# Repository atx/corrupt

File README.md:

# corrupt
A 65% keyboard with a somewhat non-standard layout. Inspired by the KBT Pure Pro.

### Specs

 * Standard GH60-style case support
 * MX-style switches
 * 2U left shift (bottom row shifted by 0.25U to the left)
 * Standard 6.25U spacebar
 * USB-C (wired-only)
 * [zmk port](https://github.com/atx/zmk/tree/corrupt)
 * Compatible FR4 plate included in the repository
 * Under-the-spacebar WE-SKEDD debugging port
 * STM32F405 MCU (total overkill)
 * Both the key plate and the PCB can be manufactured by JLC, most components are available for PCBA

### Layout

### Debugging connector

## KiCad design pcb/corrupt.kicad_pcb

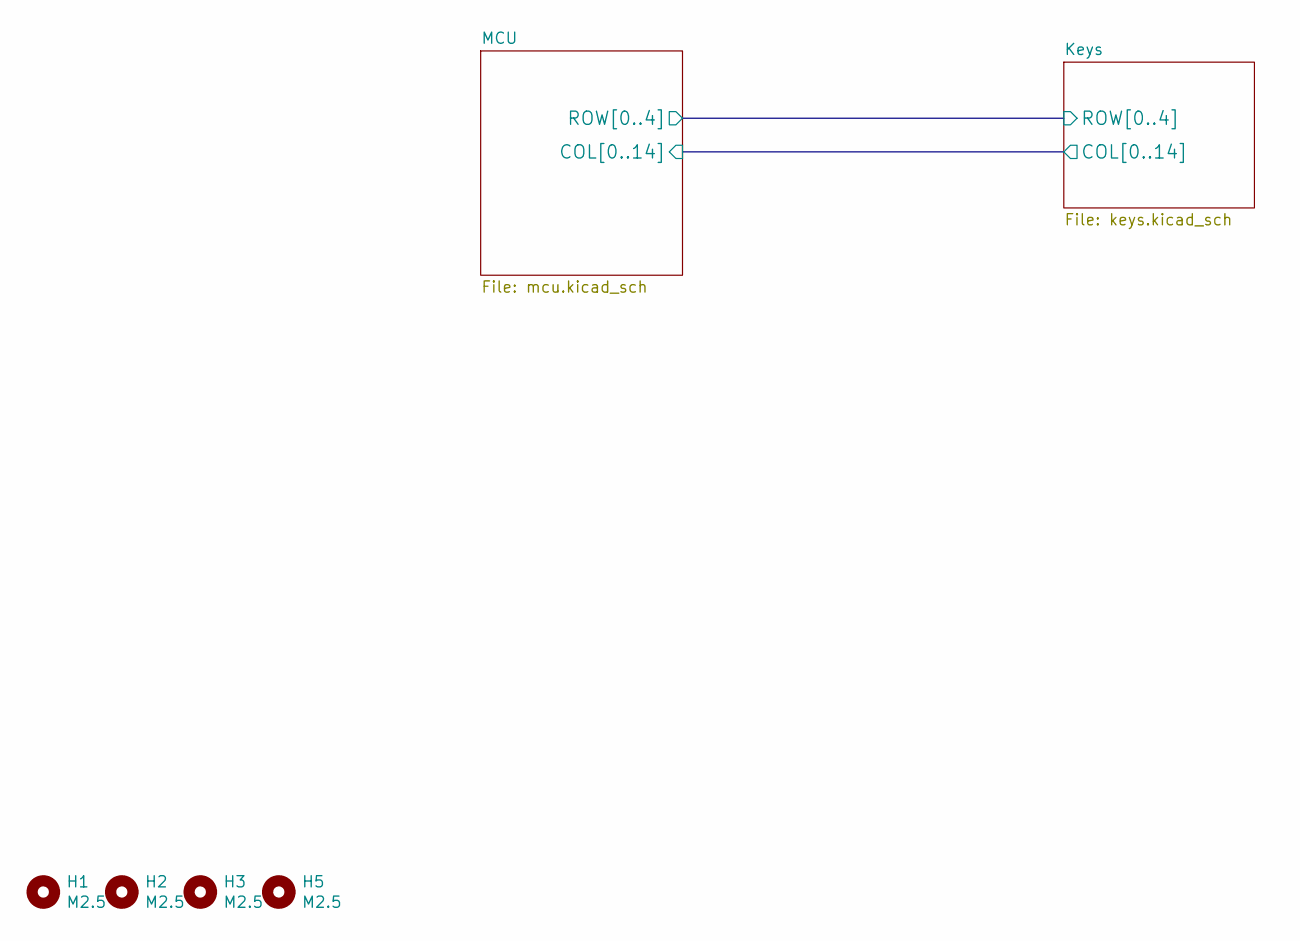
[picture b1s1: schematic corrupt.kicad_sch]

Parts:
H1, H2, H3, H5: M2.5; MountingHole_2.7mm_M2.5_Pad

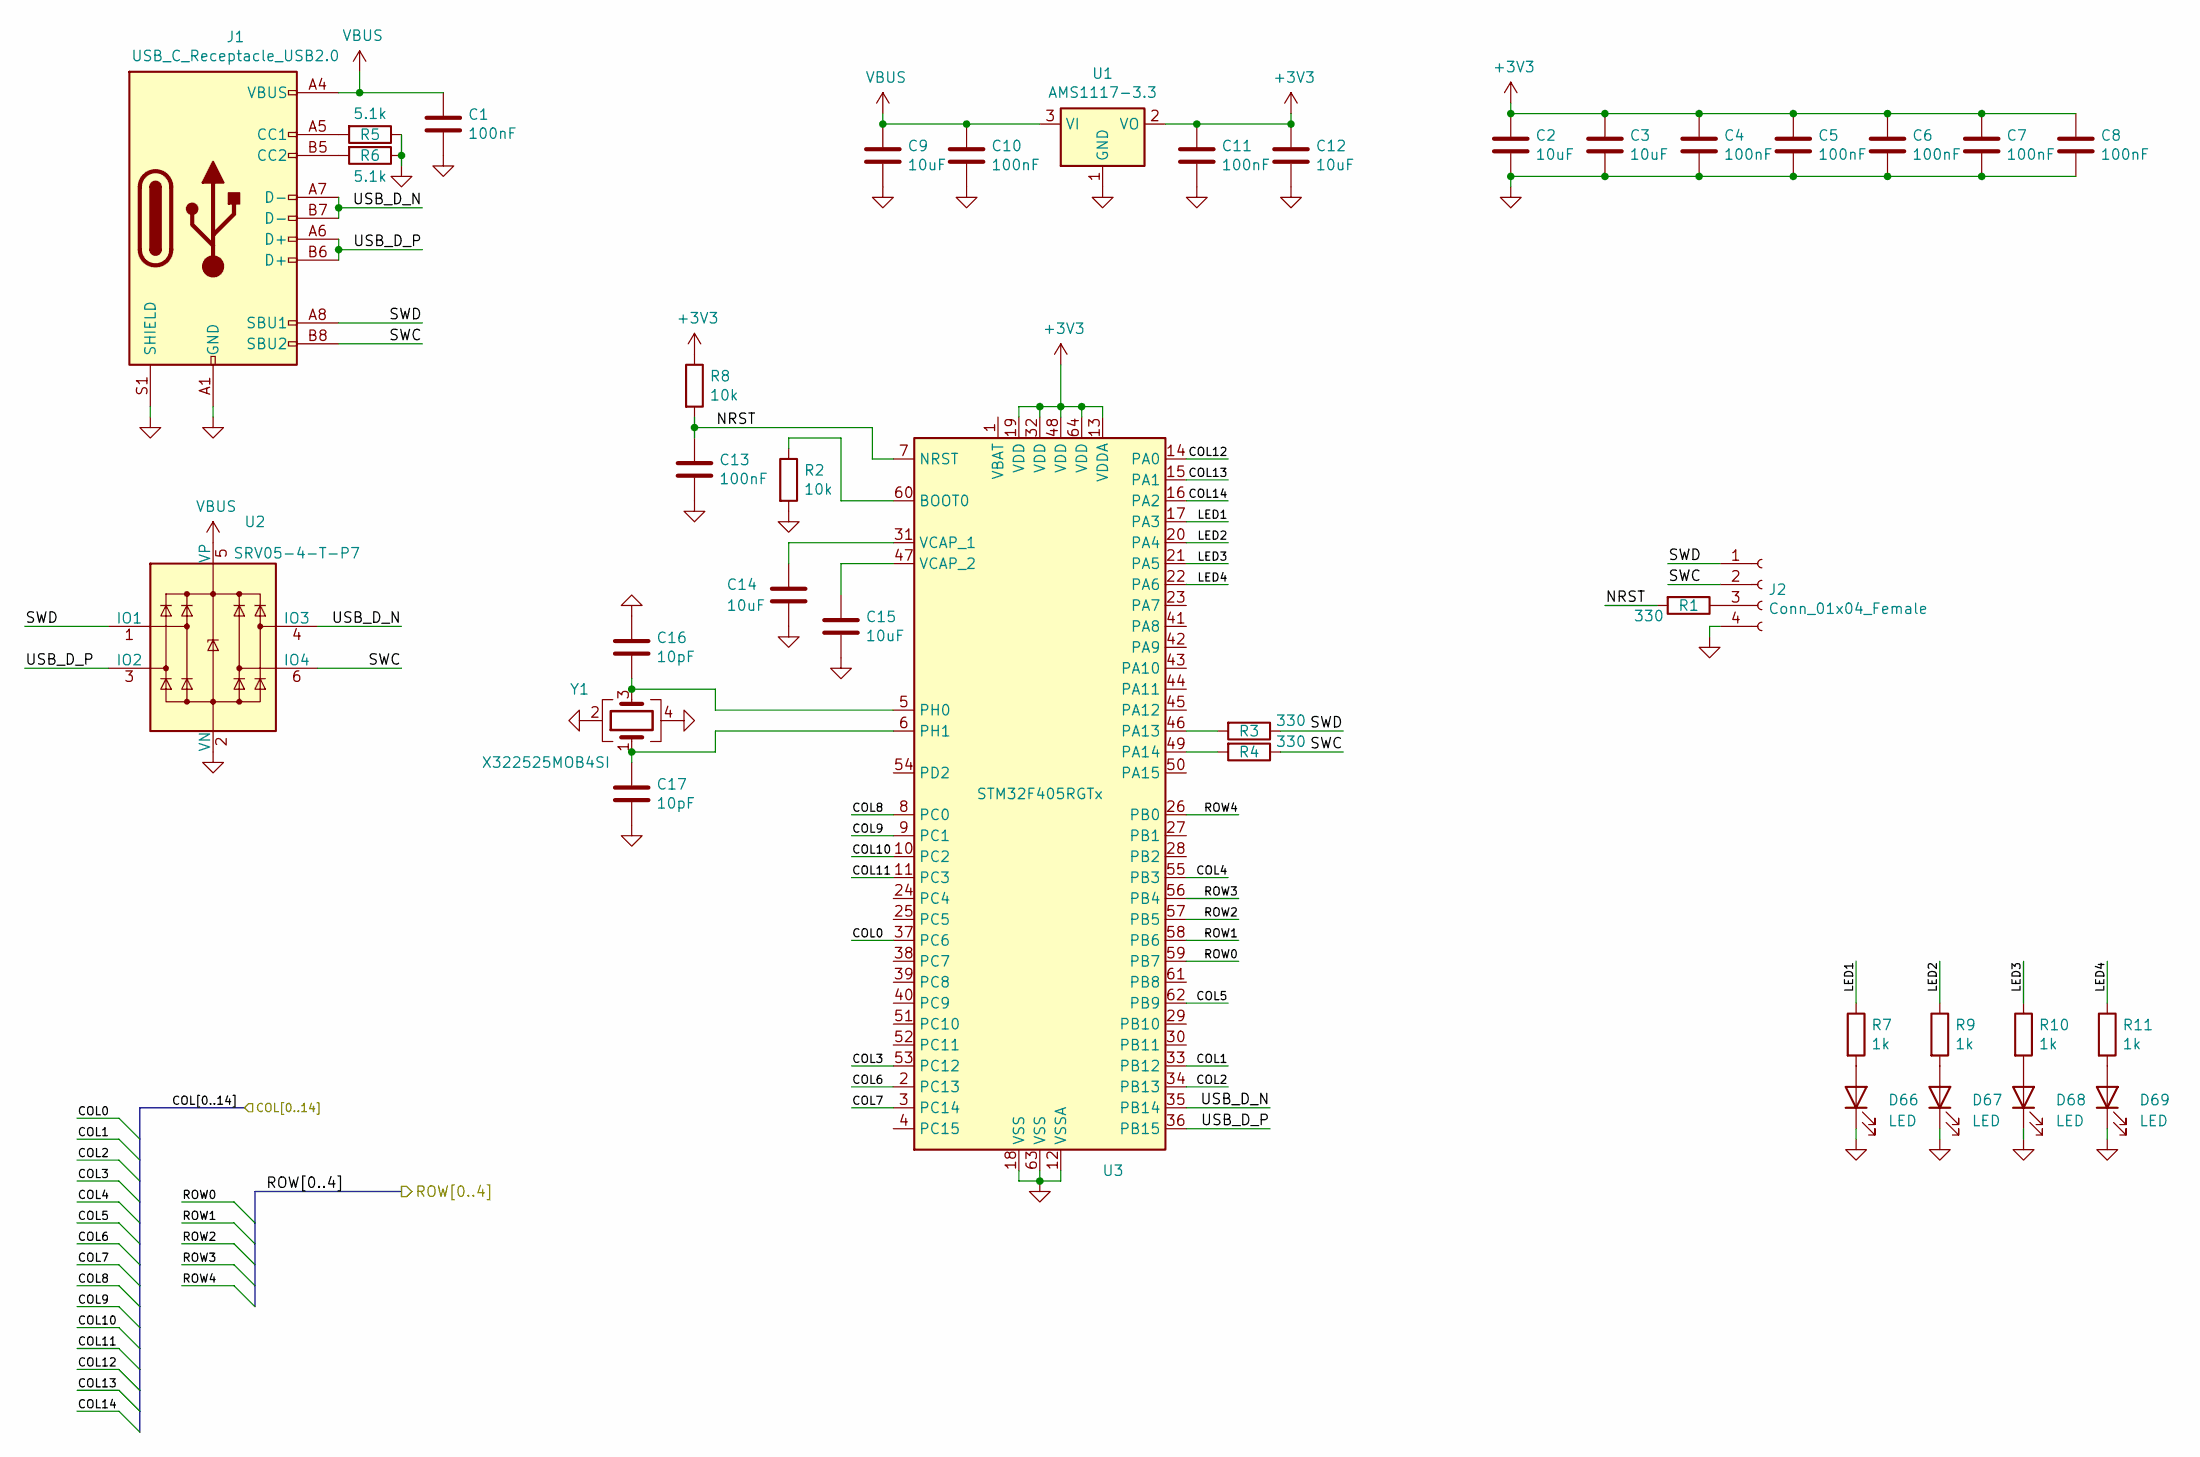
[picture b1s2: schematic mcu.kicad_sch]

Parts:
C1, C4, C5, C6, C7, C8, C10, C11, C13: 100nF; C_0402_1005Metric; LCSC C1525
C2, C3, C9, C12, C14, C15: 10uF; C_0603_1608Metric; LCSC C19702
C16, C17: 10pF; C_0402_1005Metric; LCSC C32949
D66, D67, D68, D69: LED; LED_0603_1608Metric
J1: USB_C_Receptacle_USB2.0; USB_C_Receptacle_Palconn_UTC16-G
J2: Conn_01x04_Female; WR-WST-4P-DBG
R1, R3, R4: 330; R_0402_1005Metric; LCSC C25104
R2, R8: 10k; R_0402_1005Metric; LCSC C25744
R5, R6: 5.1k; R_0402_1005Metric; LCSC C25905
R7, R9, R10, R11: 1k; R_0402_1005Metric; LCSC C11702
U1: AMS1117-3.3; SOT-223-3_TabPin2; LCSC C6186
U2: SRV05-4-T-P7; SOT-23-6; LCSC C7420376
U3: STM32F405RGTx; LQFP-64_10x10mm_P0.5mm; LCSC C15742
Y1: X322525MOB4SI; Crystal_SMD_3225-4Pin_3.2x2.5mm; LCSC C9006

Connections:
+3V3: C2.1, C3.1, C4.1, C5.1, C6.1, C7.1, C8.1, C11.1, C12.1, R8.1, U1.2 (VO), U3.13 (VDDA), U3.19 (VDD), U3.32 (VDD), U3.48 (VDD), U3.64 (VDD)
/Keys/COL0: U3.37 (PC6); also elsewhere on the board
/Keys/COL1: U3.33 (PB12); also elsewhere on the board
/Keys/COL2: U3.34 (PB13); also elsewhere on the board
/Keys/COL3: U3.53 (PC12); also elsewhere on the board
/Keys/COL4: U3.55 (PB3); also elsewhere on the board
/Keys/COL5: U3.62 (PB9); also elsewhere on the board
/Keys/COL6: U3.2 (PC13); also elsewhere on the board
/Keys/COL7: U3.3 (PC14); also elsewhere on the board
/Keys/COL8: U3.8 (PC0); also elsewhere on the board
/Keys/COL9: U3.9 (PC1); also elsewhere on the board
/Keys/COL10: U3.10 (PC2); also elsewhere on the board
/Keys/COL11: U3.11 (PC3); also elsewhere on the board
/Keys/COL12: U3.14 (PA0); also elsewhere on the board
/Keys/COL13: U3.15 (PA1); also elsewhere on the board
/Keys/COL14: U3.16 (PA2); also elsewhere on the board
/Keys/ROW0: U3.59 (PB7); also elsewhere on the board
/Keys/ROW1: U3.58 (PB6); also elsewhere on the board
/Keys/ROW2: U3.57 (PB5); also elsewhere on the board
/Keys/ROW3: U3.56 (PB4); also elsewhere on the board
/Keys/ROW4: U3.26 (PB0); also elsewhere on the board
/MCU/LED1: R7.1, U3.17 (PA3)
/MCU/LED2: R9.1, U3.20 (PA4)
/MCU/LED3: R10.1, U3.21 (PA5)
/MCU/LED4: R11.1, U3.22 (PA6)
/MCU/NRST: C13.1, R1.2, R8.2, U3.7 (NRST)
/MCU/SWC: J1.B8 (SBU2), J2.2, R4.1, U2.6 (IO4)
/MCU/SWD: J1.A8 (SBU1), J2.1, R3.1, U2.1 (IO1)
/MCU/USB_D_N: J1.A7 (D-), J1.B7 (D-), U2.4 (IO3), U3.35 (PB14)
/MCU/USB_D_P: J1.A6 (D+), J1.B6 (D+), U2.3 (IO2), U3.36 (PB15)
GND: C1.2, C2.2, C3.2, C4.2, C5.2, C6.2, C7.2, C8.2, C9.2, C10.2, C11.2, C12.2, C13.2, C14.2, C15.2, C16.1, C17.2, D66.1 (K), D67.1 (K), D68.1 (K), D69.1 (K), J1.A1 (GND), J1.A12 (GND), J1.B1 (GND), J1.B12 (GND), J1.S1 (SHIELD), J2.4, R2.2, R5.1, R6.1, U1.1 (GND), U2.2 (VN), U3.12 (VSSA), U3.18 (VSS), U3.63 (VSS), Y1.2, Y1.4
unnamed: D66.2 (A), R7.2
unnamed: D67.2 (A), R9.2
unnamed: D68.2 (A), R10.2
unnamed: D69.2 (A), R11.2
unnamed: J1.A5 (CC1), R5.2
unnamed: J1.B5 (CC2), R6.2
unnamed: J2.3, R1.1
unnamed: R2.1, U3.60 (BOOT0)
unnamed: R3.2, U3.46 (PA13)
unnamed: R4.2, U3.49 (PA14)
unnamed: C16.2, U3.5 (PH0), Y1.3
unnamed: C17.1, U3.6 (PH1), Y1.1
unnamed: C14.1, U3.31 (VCAP_1)
unnamed: C15.1, U3.47 (VCAP_2)
VBUS: C1.1, C9.1, C10.1, J1.A4 (VBUS), J1.A9 (VBUS), J1.B4 (VBUS), J1.B9 (VBUS), U1.3 (VI), U2.5 (VP)

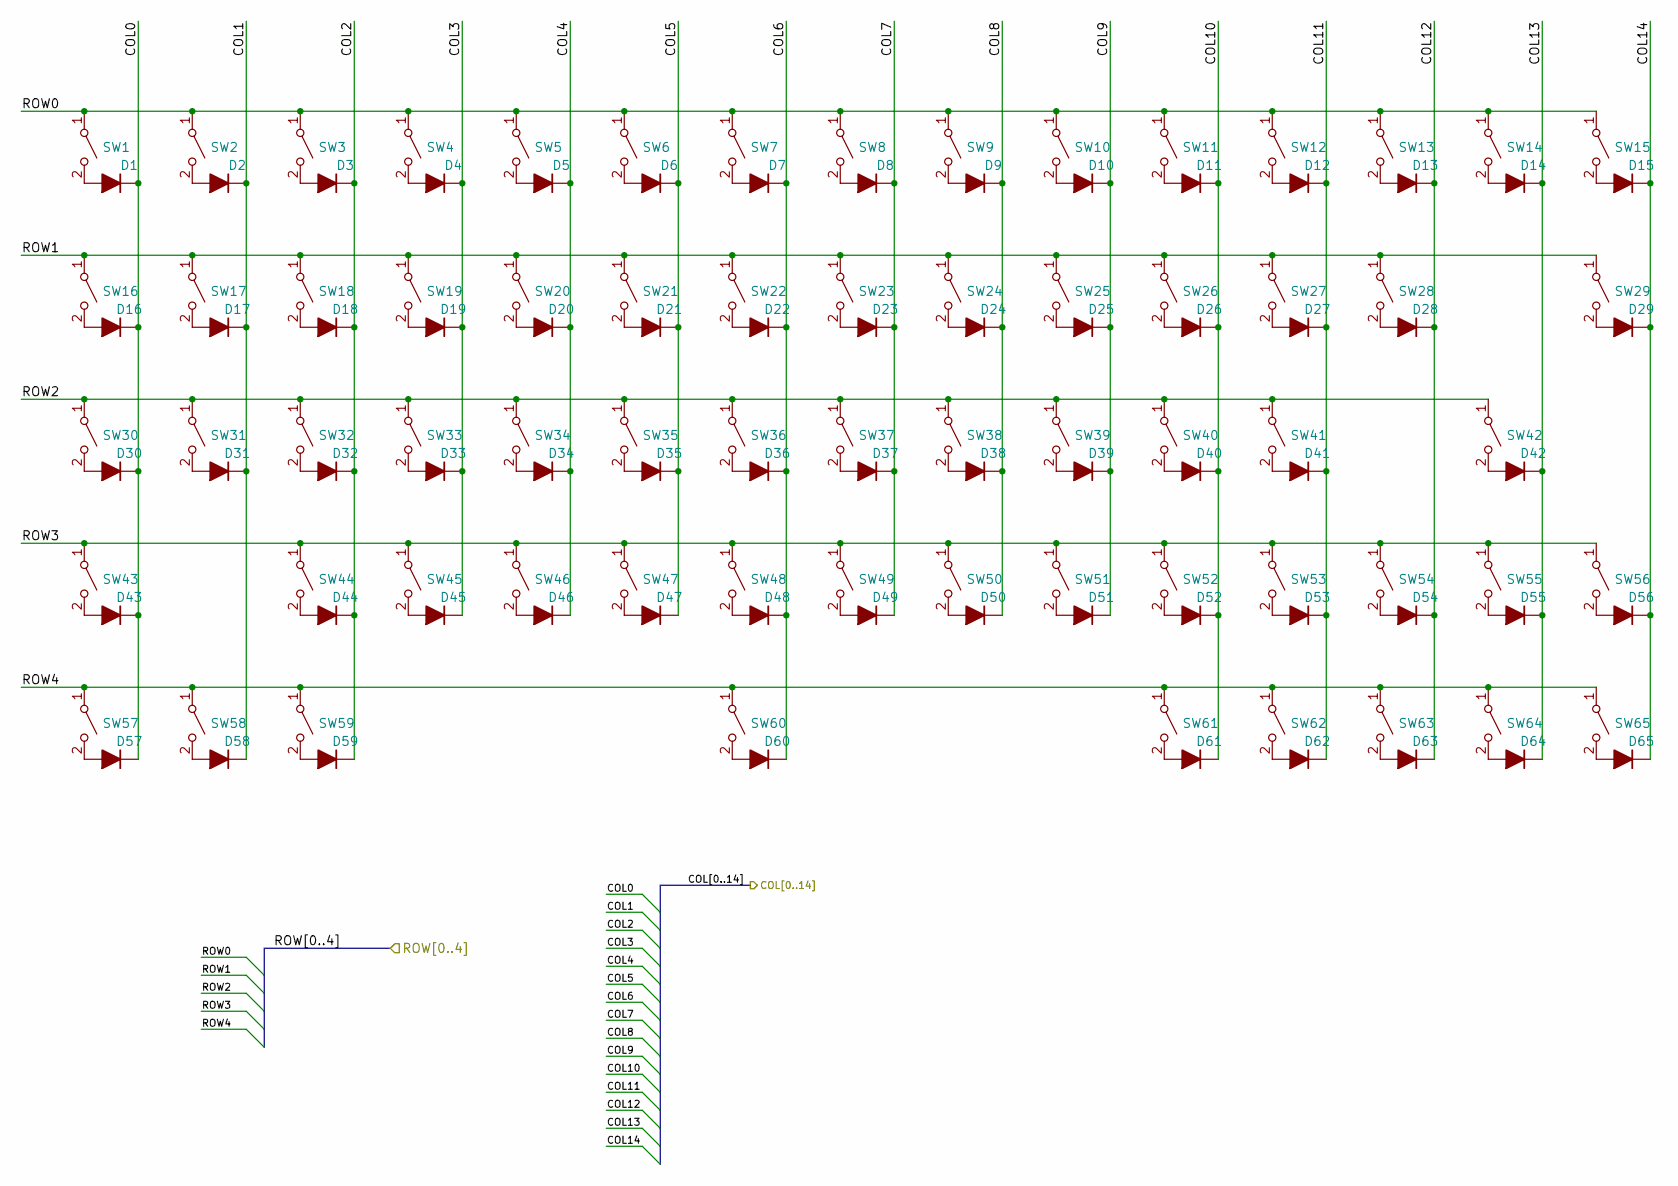
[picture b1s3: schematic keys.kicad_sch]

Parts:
D1, D2, D3, D4, D5, D6, D7, D8, D9, D10, D11, D12, D13, D14, D15, D16, D17, D18, D19, D20, D21, D22, D23, D24, D25, D26, D27, D28, D29, D30, D31, D32, D33, D34, D35, D36, D37, D38, D39, D40, D41, D42, D43, D44, D45, D46, D47, D48, D49, D50, D51, D52, D53, D54, D55, D56, D57, D58, D59, D60, D61, D62, D63, D64, D65: 1N4148WS; D_SOD-323; LCSC C2128
SW1, SW2, SW3, SW4, SW5, SW6, SW7, SW8, SW9, SW10, SW11, SW12, SW13, SW14, SW15, SW17, SW18, SW19, SW20, SW21, SW22, SW23, SW24, SW25, SW26, SW27, SW28, SW31, SW32, SW33, SW34, SW35, SW36, SW37, SW38, SW39, SW40, SW41, SW44, SW45, SW46, SW47, SW48, SW49, SW50, SW51, SW52, SW53, SW54, SW55, SW56, SW61, SW62, SW63, SW64, SW65: SW_SPST; SW_Cherry_MX_1.00u_PCB
SW16, SW29: SW_SPST; SW_Cherry_MX_1.50u_PCB
SW30: SW_SPST; SW_Cherry_MX_1.75u_PCB
SW42: SW_SPST; SW_Cherry_MX_2.25u_PCB
SW43: SW_SPST; SW_Cherry_MX_2.00u_PCB
SW57, SW58, SW59: SW_SPST; SW_Cherry_MX_1.25u_PCB
SW60: SW_SPST; SW_Cherry_MX_6.25u_PCB

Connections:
/Keys/COL0: D1.1 (K), D16.1 (K), D30.1 (K), D43.1 (K), D57.1 (K); also elsewhere on the board
/Keys/COL1: D2.1 (K), D17.1 (K), D31.1 (K), D58.1 (K); also elsewhere on the board
/Keys/COL2: D3.1 (K), D18.1 (K), D32.1 (K), D44.1 (K), D59.1 (K); also elsewhere on the board
/Keys/COL3: D4.1 (K), D19.1 (K), D33.1 (K), D45.1 (K); also elsewhere on the board
/Keys/COL4: D5.1 (K), D20.1 (K), D34.1 (K), D46.1 (K); also elsewhere on the board
/Keys/COL5: D6.1 (K), D21.1 (K), D35.1 (K), D47.1 (K); also elsewhere on the board
/Keys/COL6: D7.1 (K), D22.1 (K), D36.1 (K), D48.1 (K), D60.1 (K); also elsewhere on the board
/Keys/COL7: D8.1 (K), D23.1 (K), D37.1 (K), D49.1 (K); also elsewhere on the board
/Keys/COL8: D9.1 (K), D24.1 (K), D38.1 (K), D50.1 (K); also elsewhere on the board
/Keys/COL9: D10.1 (K), D25.1 (K), D39.1 (K), D51.1 (K); also elsewhere on the board
/Keys/COL10: D11.1 (K), D26.1 (K), D40.1 (K), D52.1 (K), D61.1 (K); also elsewhere on the board
/Keys/COL11: D12.1 (K), D27.1 (K), D41.1 (K), D53.1 (K), D62.1 (K); also elsewhere on the board
/Keys/COL12: D13.1 (K), D28.1 (K), D54.1 (K), D63.1 (K); also elsewhere on the board
/Keys/COL13: D14.1 (K), D42.1 (K), D55.1 (K), D64.1 (K); also elsewhere on the board
/Keys/COL14: D15.1 (K), D29.1 (K), D56.1 (K), D65.1 (K); also elsewhere on the board
/Keys/ROW0: SW1.1 (A), SW2.1 (A), SW3.1 (A), SW4.1 (A), SW5.1 (A), SW6.1 (A), SW7.1 (A), SW8.1 (A), SW9.1 (A), SW10.1 (A), SW11.1 (A), SW12.1 (A), SW13.1 (A), SW14.1 (A), SW15.1 (A); also elsewhere on the board
/Keys/ROW1: SW16.1 (A), SW17.1 (A), SW18.1 (A), SW19.1 (A), SW20.1 (A), SW21.1 (A), SW22.1 (A), SW23.1 (A), SW24.1 (A), SW25.1 (A), SW26.1 (A), SW27.1 (A), SW28.1 (A), SW29.1 (A); also elsewhere on the board
/Keys/ROW2: SW30.1 (A), SW31.1 (A), SW32.1 (A), SW33.1 (A), SW34.1 (A), SW35.1 (A), SW36.1 (A), SW37.1 (A), SW38.1 (A), SW39.1 (A), SW40.1 (A), SW41.1 (A), SW42.1 (A); also elsewhere on the board
/Keys/ROW3: SW43.1 (A), SW44.1 (A), SW45.1 (A), SW46.1 (A), SW47.1 (A), SW48.1 (A), SW49.1 (A), SW50.1 (A), SW51.1 (A), SW52.1 (A), SW53.1 (A), SW54.1 (A), SW55.1 (A), SW56.1 (A); also elsewhere on the board
/Keys/ROW4: SW57.1 (A), SW58.1 (A), SW59.1 (A), SW60.1 (A), SW61.1 (A), SW62.1 (A), SW63.1 (A), SW64.1 (A), SW65.1 (A); also elsewhere on the board
unnamed: D1.2 (A), SW1.2 (B)
unnamed: D2.2 (A), SW2.2 (B)
unnamed: D3.2 (A), SW3.2 (B)
unnamed: D4.2 (A), SW4.2 (B)
unnamed: D5.2 (A), SW5.2 (B)
unnamed: D6.2 (A), SW6.2 (B)
unnamed: D7.2 (A), SW7.2 (B)
unnamed: D8.2 (A), SW8.2 (B)
unnamed: D9.2 (A), SW9.2 (B)
unnamed: D10.2 (A), SW10.2 (B)
unnamed: D11.2 (A), SW11.2 (B)
unnamed: D12.2 (A), SW12.2 (B)
unnamed: D13.2 (A), SW13.2 (B)
unnamed: D14.2 (A), SW14.2 (B)
unnamed: D15.2 (A), SW15.2 (B)
unnamed: D16.2 (A), SW16.2 (B)
unnamed: D17.2 (A), SW17.2 (B)
unnamed: D18.2 (A), SW18.2 (B)
unnamed: D19.2 (A), SW19.2 (B)
unnamed: D20.2 (A), SW20.2 (B)
unnamed: D21.2 (A), SW21.2 (B)
unnamed: D22.2 (A), SW22.2 (B)
unnamed: D23.2 (A), SW23.2 (B)
unnamed: D24.2 (A), SW24.2 (B)
unnamed: D25.2 (A), SW25.2 (B)
unnamed: D26.2 (A), SW26.2 (B)
unnamed: D27.2 (A), SW27.2 (B)
unnamed: D28.2 (A), SW28.2 (B)
unnamed: D29.2 (A), SW29.2 (B)
unnamed: D30.2 (A), SW30.2 (B)
unnamed: D31.2 (A), SW31.2 (B)
unnamed: D32.2 (A), SW32.2 (B)
unnamed: D33.2 (A), SW33.2 (B)
unnamed: D34.2 (A), SW34.2 (B)
unnamed: D35.2 (A), SW35.2 (B)
unnamed: D36.2 (A), SW36.2 (B)
unnamed: D37.2 (A), SW37.2 (B)
unnamed: D38.2 (A), SW38.2 (B)
unnamed: D39.2 (A), SW39.2 (B)
unnamed: D40.2 (A), SW40.2 (B)
unnamed: D41.2 (A), SW41.2 (B)
unnamed: D42.2 (A), SW42.2 (B)
unnamed: D43.2 (A), SW43.2 (B)
unnamed: D44.2 (A), SW44.2 (B)
unnamed: D45.2 (A), SW45.2 (B)
unnamed: D46.2 (A), SW46.2 (B)
unnamed: D47.2 (A), SW47.2 (B)
unnamed: D48.2 (A), SW48.2 (B)
unnamed: D49.2 (A), SW49.2 (B)
unnamed: D50.2 (A), SW50.2 (B)
unnamed: D51.2 (A), SW51.2 (B)
unnamed: D52.2 (A), SW52.2 (B)
unnamed: D53.2 (A), SW53.2 (B)
unnamed: D54.2 (A), SW54.2 (B)
unnamed: D55.2 (A), SW55.2 (B)
unnamed: D56.2 (A), SW56.2 (B)
unnamed: D57.2 (A), SW57.2 (B)
unnamed: D58.2 (A), SW58.2 (B)
unnamed: D59.2 (A), SW59.2 (B)
unnamed: D60.2 (A), SW60.2 (B)
unnamed: D61.2 (A), SW61.2 (B)
unnamed: D62.2 (A), SW62.2 (B)
unnamed: D63.2 (A), SW63.2 (B)
unnamed: D64.2 (A), SW64.2 (B)
unnamed: D65.2 (A), SW65.2 (B)

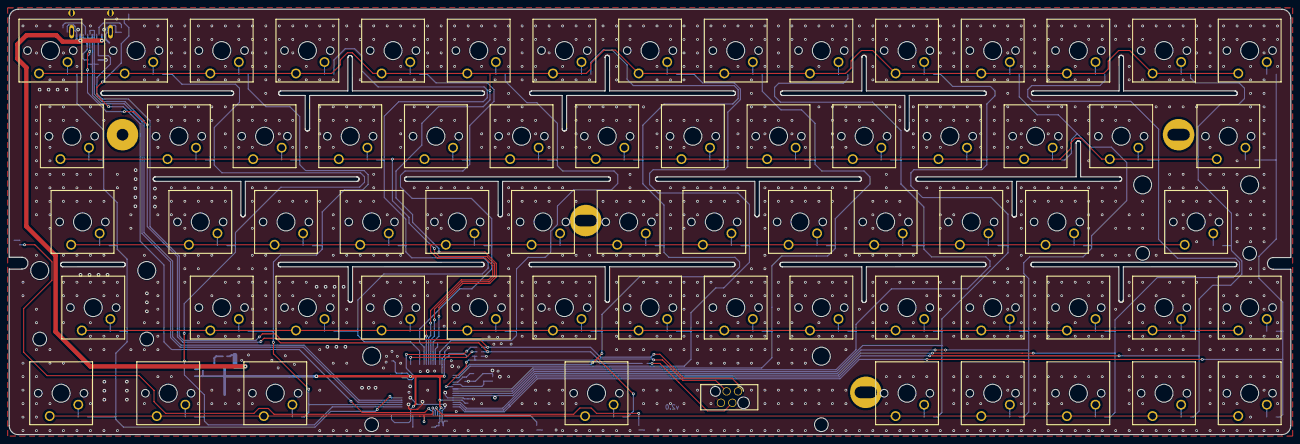
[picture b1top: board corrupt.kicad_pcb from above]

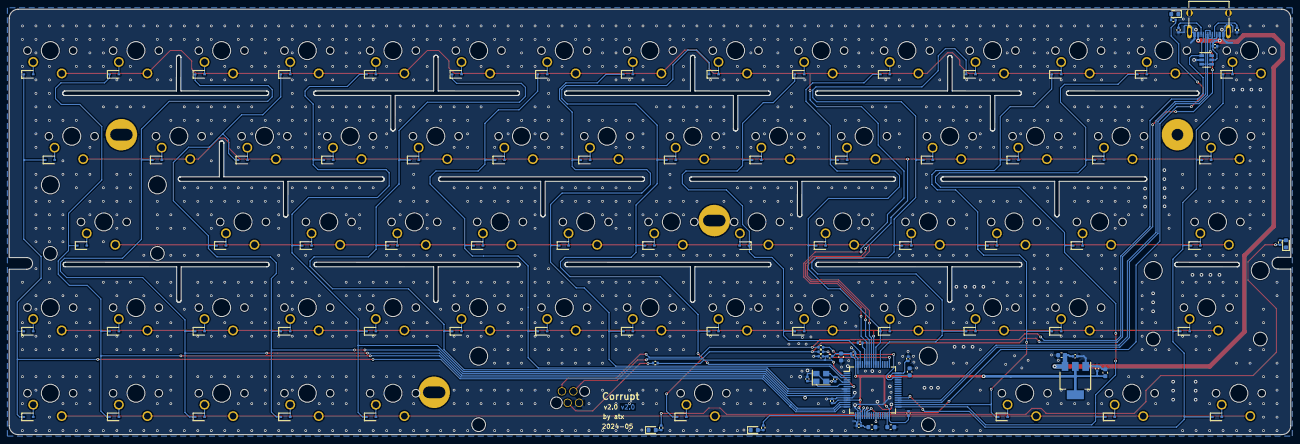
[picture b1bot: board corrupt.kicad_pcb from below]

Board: 2 copper layers, 285.0 x 94.6 mm, 172 parts (102 on the bottom side), 111 nets.

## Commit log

2021-01-30 pcb: v1.0
    Initial PCB version
2021-04-28 zmk: Add zmk-config
2024-07-05 Update to KiCad 8
2024-07-05 pcb: v2.0
